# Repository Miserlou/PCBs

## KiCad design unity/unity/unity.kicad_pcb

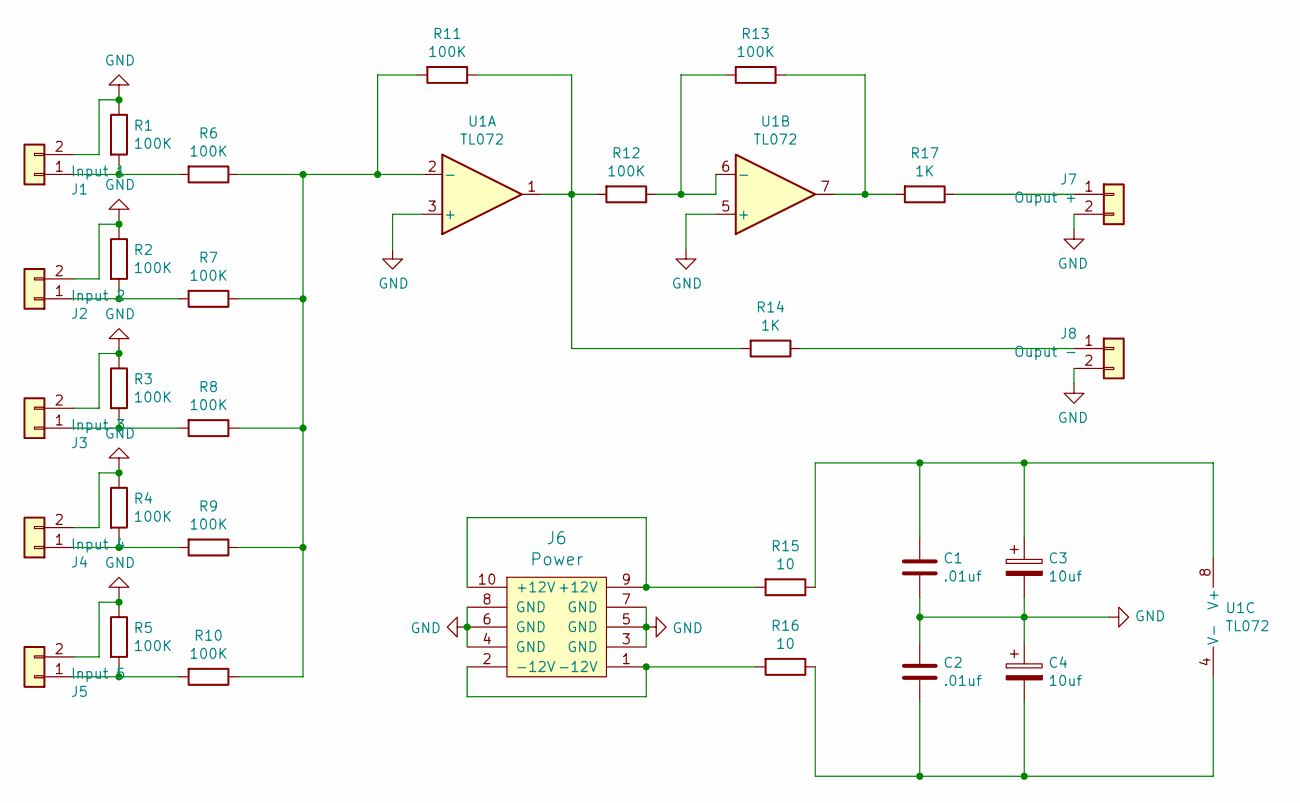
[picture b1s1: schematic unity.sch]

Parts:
C1, C2: .01uf; C_Disc_D3.0mm_W1.6mm_P2.50mm
C3, C4: 10uf; CP_Radial_D5.0mm_P2.00mm
J1: Input 1; Molex_KK-254_AE-6410-02A_1x02_P2.54mm_Vertical
J2: Input 2; Molex_KK-254_AE-6410-02A_1x02_P2.54mm_Vertical
J3: Input 3; Molex_KK-254_AE-6410-02A_1x02_P2.54mm_Vertical
J4: Input 4; Molex_KK-254_AE-6410-02A_1x02_P2.54mm_Vertical
J5: Input 5; Molex_KK-254_AE-6410-02A_1x02_P2.54mm_Vertical
J6: Power; Power_Header
J7: Ouput +; Molex_KK-254_AE-6410-02A_1x02_P2.54mm_Vertical
J8: Ouput -; Molex_KK-254_AE-6410-02A_1x02_P2.54mm_Vertical
R1, R2, R3, R4, R5, R6, R7, R8, R9, R10, R11, R12, R13: 100K; R_Axial_DIN0207_L6.3mm_D2.5mm_P7.62mm_Horizontal
R14, R17: 1K; R_Axial_DIN0207_L6.3mm_D2.5mm_P7.62mm_Horizontal
R15, R16: 10; R_Axial_DIN0207_L6.3mm_D2.5mm_P7.62mm_Horizontal
U1: TL072; DIP-8_W7.62mm_Socket_LongPads

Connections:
GND: C1.2, C2.1, C3.2, C4.1, J1.2, J2.2, J3.2, J4.2, J5.2, J6.3 (GND), J6.4 (GND), J6.5 (GND), J6.6 (GND), J6.7 (GND), J6.8 (GND), J7.2, J8.2, R1.1, R2.1, R3.1, R4.1, R5.1, U1.3 (+), U1.5 (+)
unnamed: C1.1, C3.1, R15.1, U1.8 (V+)
unnamed: C2.2, C4.2, R16.1, U1.4 (V-)
unnamed: J1.1, R1.2, R6.2
unnamed: J2.1, R2.2, R7.2
unnamed: J3.1, R3.2, R8.2
unnamed: J4.1, R4.2, R9.2
unnamed: J5.1, R5.2, R10.2
unnamed: J6.1 (-12V), J6.2 (-12V), R16.2
unnamed: J6.9 (+12V), J6.10 (+12V), R15.2
unnamed: J7.1, R17.1
unnamed: J8.1, R14.1
unnamed: R6.1, R7.1, R8.1, R9.1, R10.1, R11.2, U1.2 (-)
unnamed: R11.1, R12.2, R14.2, U1.1
unnamed: R12.1, R13.2, U1.6 (-)
unnamed: R13.1, R17.2, U1.7

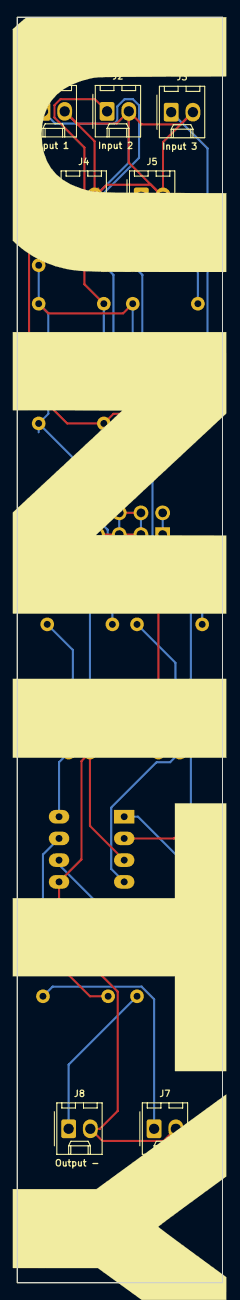
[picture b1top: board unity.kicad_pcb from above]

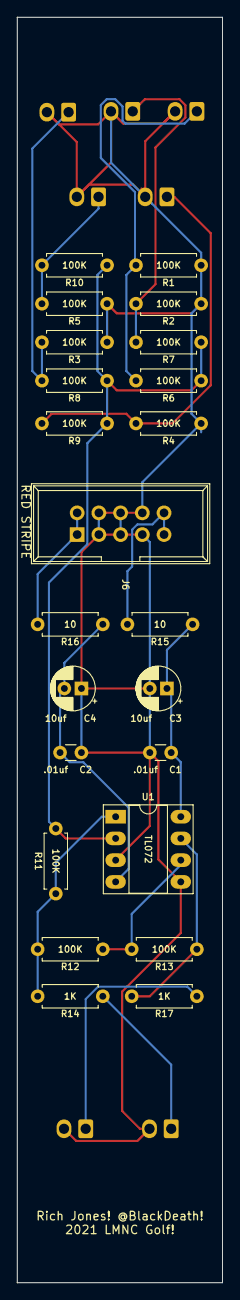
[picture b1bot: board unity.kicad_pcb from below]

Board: 2 copper layers, 24.0 x 148.0 mm, 30 parts (23 on the bottom side), 16 nets.

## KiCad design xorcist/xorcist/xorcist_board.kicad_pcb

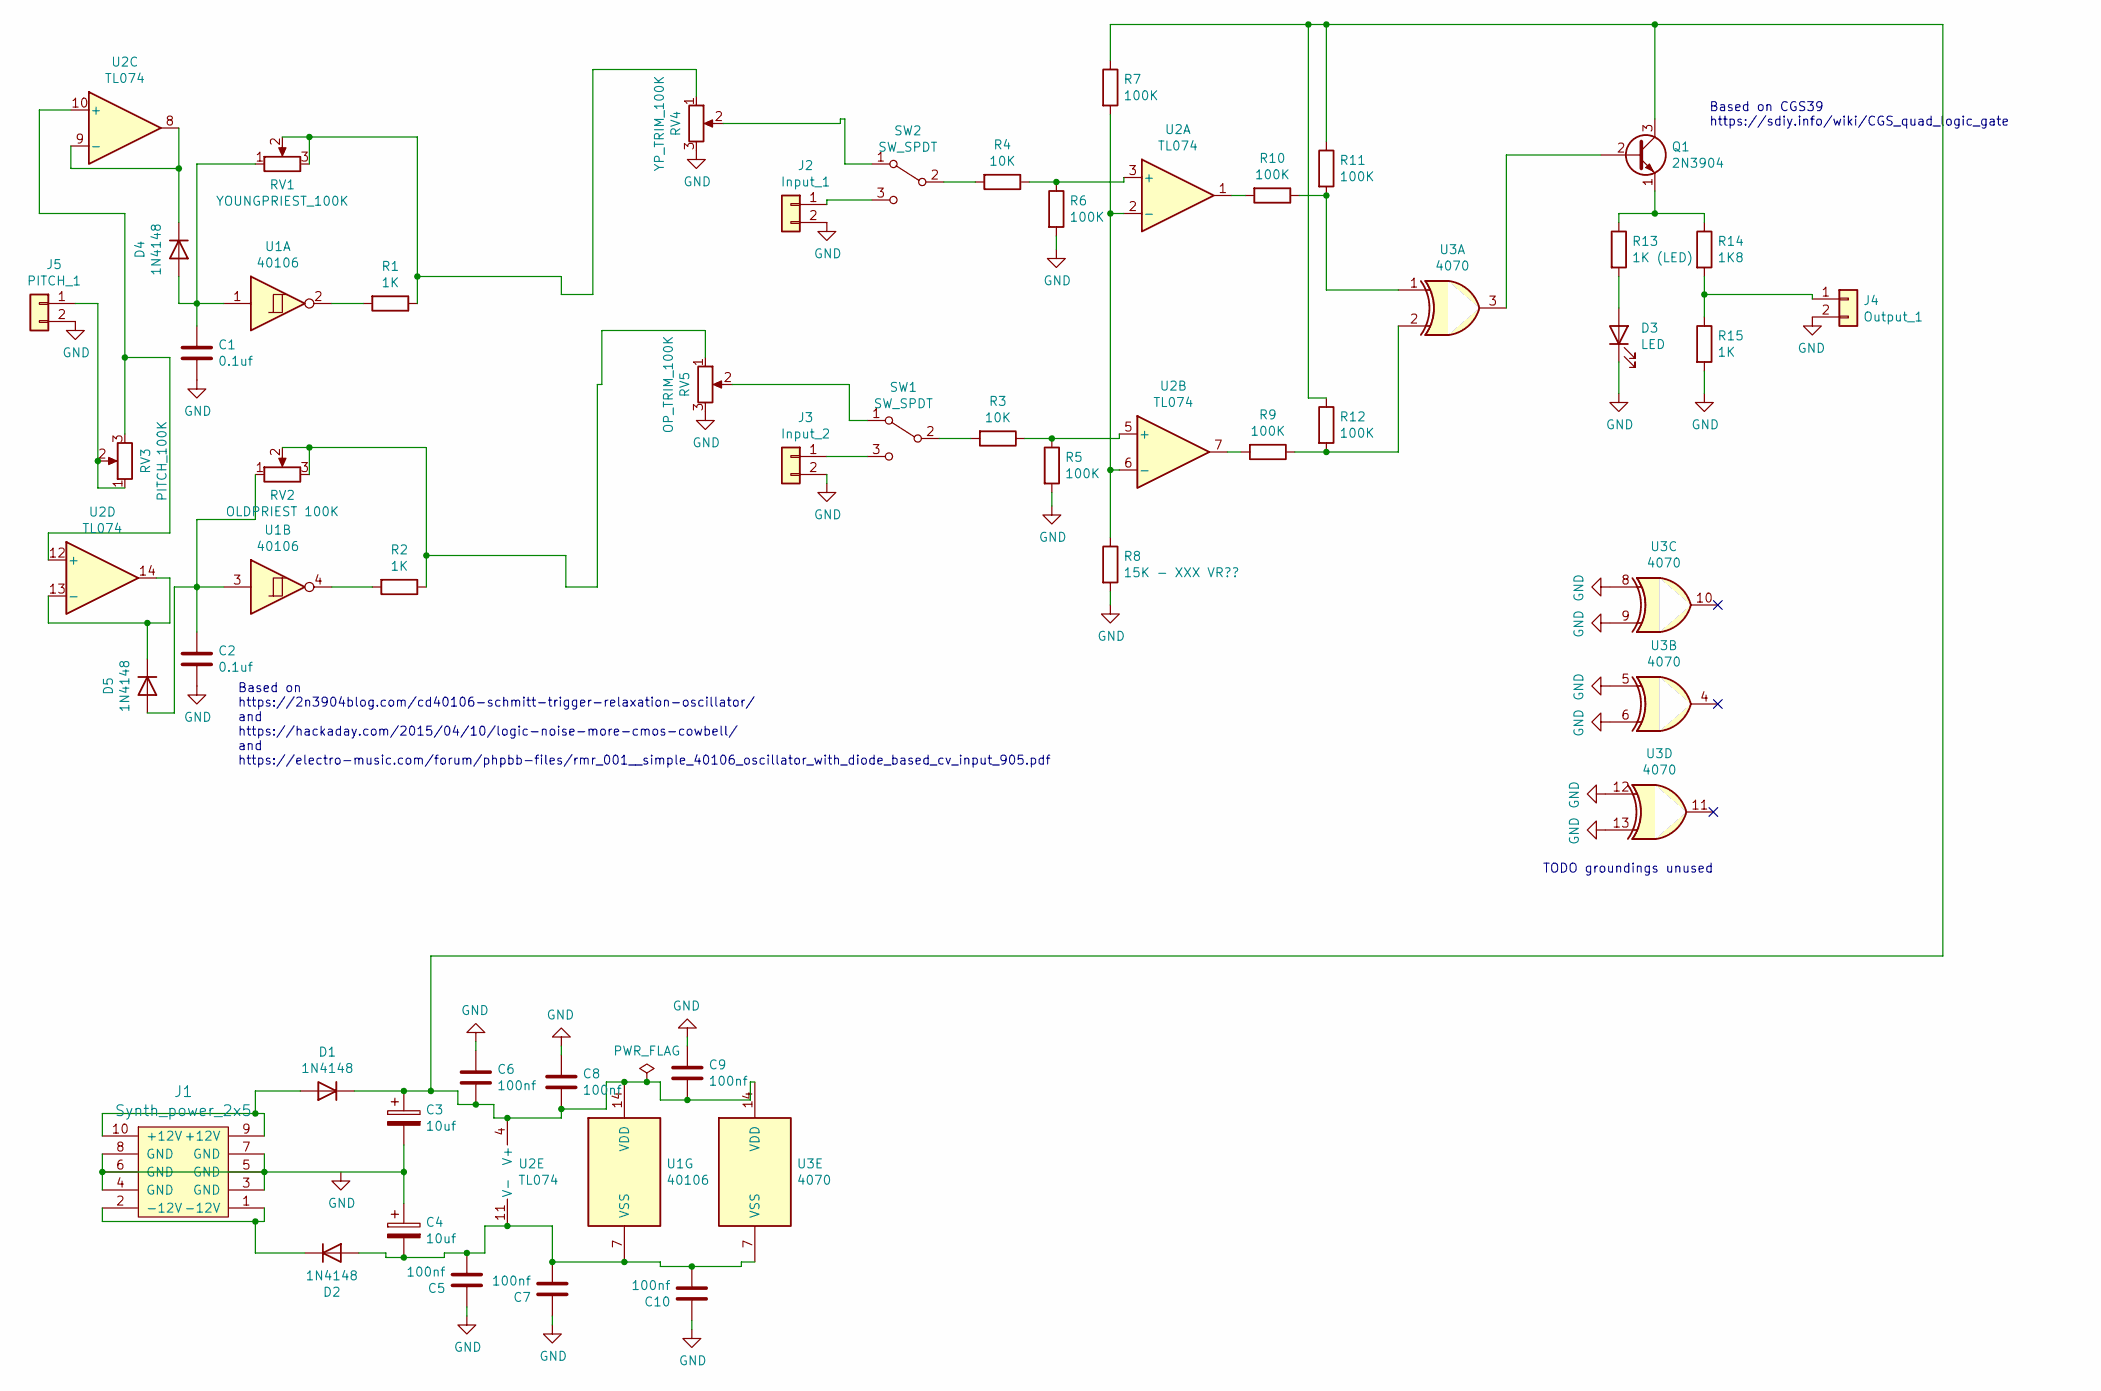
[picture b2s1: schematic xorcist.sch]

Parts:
C1, C2: 0.1uf; C_Disc_D3.0mm_W1.6mm_P2.50mm
C3, C4: 10uf; CP_Radial_D6.3mm_P2.50mm
C5, C6, C7, C8, C9, C10: 100nf; C_Disc_D3.0mm_W1.6mm_P2.50mm
D1, D2, D4, D5: 1N4148; D_DO-35_SOD27_P7.62mm_Horizontal
D3: LED; LED_D5.0mm
J1: Synth_power_2x5; Power_Header
J2: Input_1; Molex_KK-254_AE-6410-02A_1x02_P2.54mm_Vertical
J3: Input_2; Molex_KK-254_AE-6410-02A_1x02_P2.54mm_Vertical
J4: Output_1; Molex_KK-254_AE-6410-02A_1x02_P2.54mm_Vertical
J5: PITCH_1; Molex_KK-254_AE-6410-02A_1x02_P2.54mm_Vertical
Q1: 2N3904; TO-92_Inline_Wide
R1, R2, R15: 1K; R_Axial_DIN0207_L6.3mm_D2.5mm_P10.16mm_Horizontal
R3, R4: 10K; R_Axial_DIN0207_L6.3mm_D2.5mm_P10.16mm_Horizontal
R5, R6, R7, R9, R10, R11, R12: 100K; R_Axial_DIN0207_L6.3mm_D2.5mm_P10.16mm_Horizontal
R8: 15K - XXX VR??; R_Axial_DIN0207_L6.3mm_D2.5mm_P10.16mm_Horizontal
R13: 1K (LED); R_Axial_DIN0207_L6.3mm_D2.5mm_P10.16mm_Horizontal
R14: 1K8; R_Axial_DIN0207_L6.3mm_D2.5mm_P10.16mm_Horizontal
RV1: YOUNGPRIEST_100K; Potentiometer_Alpha_RD901F-40-00D_Single_Vertical_CircularH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
RV2: OLDPRIEST 100K; Potentiometer_Alpha_RD901F-40-00D_Single_Vertical_CircularH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
RV3: PITCH_100K; Potentiometer_Alpha_RD901F-40-00D_Single_Vertical_CircularH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
RV4: YP_TRIM_100K; Potentiometer_Bourns_3296W_Vertical_standard
RV5: OP_TRIM_100K; Potentiometer_Bourns_3296W_Vertical_standard
SW1, SW2: SW_SPDT; SPDT-toggle-switch-1M-series
U1: 40106; DIP-14_W7.62mm_Socket_LongPads
U2: TL074; DIP-16_W7.62mm_Socket_LongPads
U3: 4070; DIP-14_W7.62mm_Socket_LongPads

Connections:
unnamed: C1.1, D4.2 (A), RV1.1, U1.1
unnamed: C2.1, D5.2 (A), RV2.1, U1.3
unnamed: C3.1, C6.2, C8.2, C9.2, D1.1 (K), Q1.3 (C), R7.1, R11.1, R12.1, U1.14 (VDD), U2.4 (V+), U3.14 (VDD)
unnamed: C4.2, C5.2, C7.2, C10.2, D2.2 (A), U1.7 (VSS), U2.11 (V-), U3.7 (VSS)
unnamed: D1.2 (A), J1.9 (+12V), J1.10 (+12V)
unnamed: D2.1 (K), J1.1 (-12V), J1.2 (-12V)
unnamed: D3.2 (A), R13.2
unnamed: D4.1 (K), U2.8, U2.9 (-)
unnamed: D5.1 (K), U2.13 (-), U2.14
unnamed 9: J2.1, SW2.3 (C); also elsewhere on the board
unnamed 10: J3.1, SW1.3 (C); also elsewhere on the board
unnamed 11: J4.1, R14.2, R15.1; also elsewhere on the board
unnamed 12: J5.1, RV3.1, RV3.2; also elsewhere on the board
unnamed: Q1.1 (E), R13.1, R14.1
unnamed: Q1.2 (B), U3.3
unnamed: R1.1, RV1.2, RV1.3, RV4.1
unnamed: R1.2, U1.2
unnamed: R2.1, RV2.2, RV2.3, RV5.1
unnamed: R2.2, U1.4
unnamed: R3.1, R5.1, U2.5 (+)
unnamed: R3.2, SW1.2 (B)
unnamed: R4.1, R6.1, U2.3 (+)
unnamed: R4.2, SW2.2 (B)
unnamed: R7.2, R8.1, U2.2 (-), U2.6 (-)
unnamed: R9.2, U2.7
unnamed: R10.1, R11.2, U3.1
unnamed: R10.2, U2.1
unnamed: R9.1, R12.2, U3.2
unnamed: RV3.3, U2.10 (+), U2.12 (+)
unnamed: RV4.2, SW2.1 (A)
unnamed: RV5.2, SW1.1 (A)

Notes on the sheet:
Based on CGS39 https://sdiy.info/wiki/CGS_quad_logic_gate
Based on https://2n3904blog.com/cd40106-schmitt-trigger-relaxation-oscillator/ and https://hackaday.com/2015/04/10/logic-noise-more-cmos-cowbell/ and https://electro-music.com/forum/phpbb-files/rmr_001__simple_40106_oscillator_with_diode_based_cv_input_905.pdf
TODO groundings unused

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
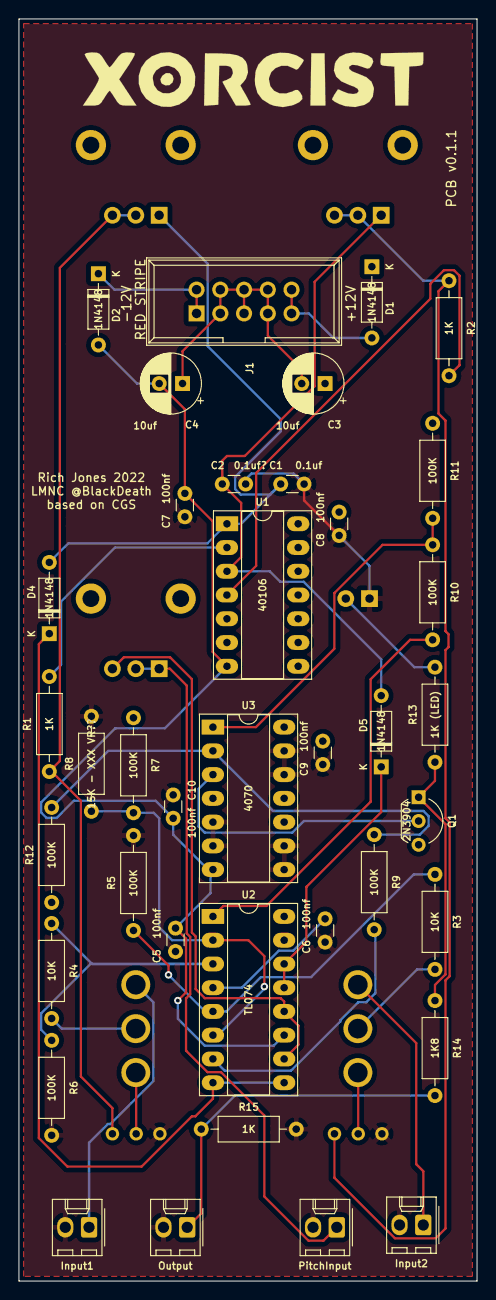
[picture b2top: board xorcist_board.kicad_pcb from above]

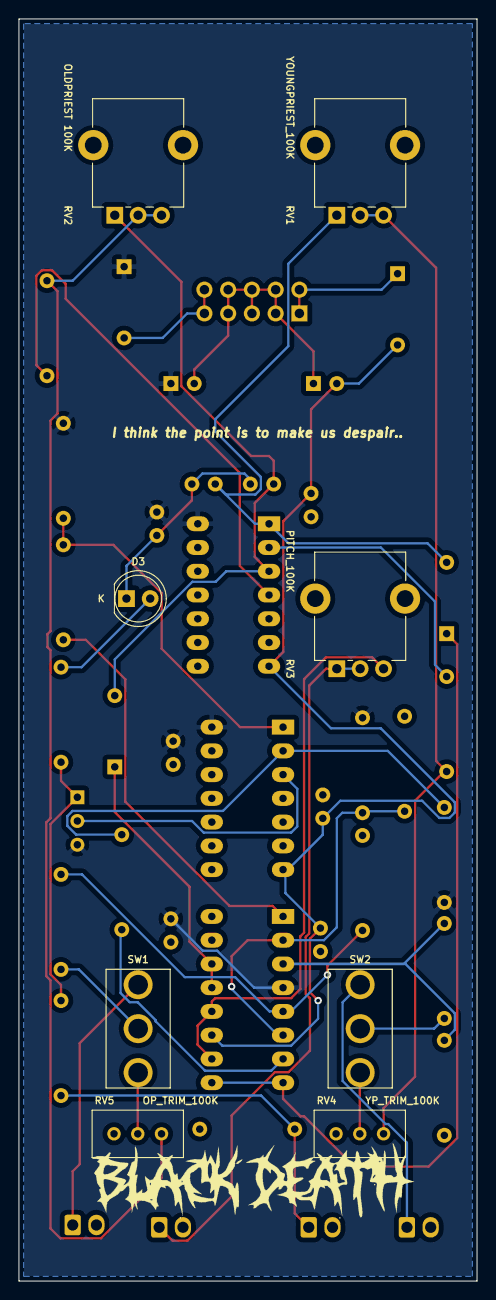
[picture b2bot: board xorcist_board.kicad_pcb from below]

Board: 2 copper layers, 49.0 x 135.0 mm, 46 parts (8 on the bottom side), 33 nets.

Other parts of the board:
Input1: Input_1; Molex_KK-254_AE-6410-02A_1x02_P2.54mm_Vertical
Input2: Input_2; Molex_KK-254_AE-6410-02A_1x02_P2.54mm_Vertical
Output: Output_1; Molex_KK-254_AE-6410-02A_1x02_P2.54mm_Vertical
PitchInput: PITCH_1; Molex_KK-254_AE-6410-02A_1x02_P2.54mm_Vertical

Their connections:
unnamed 9: Input1.1; also elsewhere on the board
unnamed 10: Input2.1; also elsewhere on the board
unnamed 11: Output.1; also elsewhere on the board
unnamed 12: PitchInput.1; also elsewhere on the board
